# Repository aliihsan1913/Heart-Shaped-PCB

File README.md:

# Heart-Shaped LED PCB Design 

## Overview
This project features a custom heart-shaped PCB designed using **KiCad 9.0**. The goal was to combine electrical functionality with a unique form factor, suitable for decorative electronics or gift projects. 

## Visuals

*Figure 1: 3D Render of the heart-shaped board.*

*Figure 2: Complete circuit schematic.*

## Technical Details
* **CAD Tool:** KiCad 9.0
* **Shape:** Custom Heart Outline (Calculated using mathematical curves/coordinates).
* **Trace Design:** Curved traces to match the board's aesthetic.

## Components List
* **Light Emitting Diodes (LEDs):** 20x Red or Pink (SMD 0805 Package) arranged in a heart contour.
* **Power Source:** 3V CR2032 Coin Cell Battery (Düğme Pil).
* **Safety Feature:** Integrated PTC Fuse for overcurrent protection.
* **Control:** Mini Slide Switch (SPDT) for ON/OFF functionality.
* **Resistors:** 120Ω or 220Ω (SMD 0805) current-limiting resistors for LED longevity.
* **PCB:** Custom FR-4 substrate with a thickness of 1.6mm.

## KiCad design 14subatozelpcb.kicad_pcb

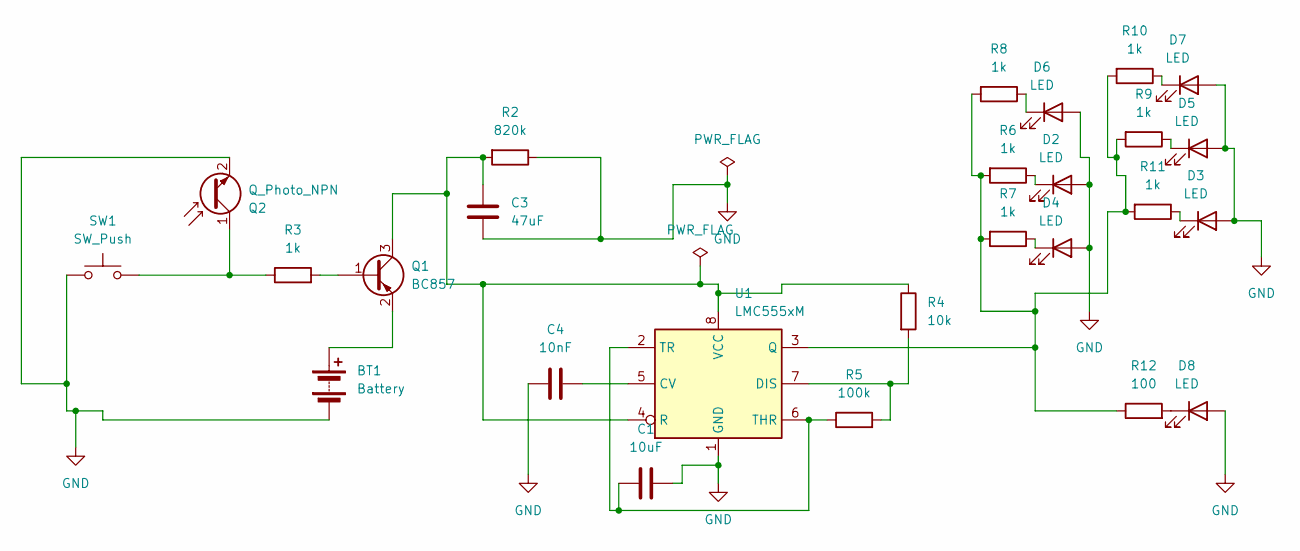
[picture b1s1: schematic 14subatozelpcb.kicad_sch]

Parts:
BT1: Battery; BatteryHolder_Keystone_3002_1x2032
C1: 10uF; R_0805_2012Metric
C3: 47uF; CP_EIA-3216-18_Kemet-A
C4: 10nF; R_0805_2012Metric
D2, D3, D4, D5, D6, D7, D8: LED; LED_0805_2012Metric
Q1: BC857; SOT-23
Q2: Q_Photo_NPN; SOT-23
R2: 820k; R_0805_2012Metric
R3, R6, R7, R8, R9, R10, R11: 1k; R_0805_2012Metric
R4: 10k; R_0805_2012Metric
R5: 100k; R_0805_2012Metric
R12: 100; R_0805_2012Metric
SW1: SW_Push; SW_SPST_TL3342
U1: LMC555xM; SOIC-8_3.9x4.9mm_P1.27mm

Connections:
GND: BT1.2 (-), C1.2, C3.2, C4.2, D2.2 (A), D3.2 (A), D4.2 (A), D5.2 (A), D6.2 (A), D7.2 (A), D8.2 (A), Q2.2 (E), R2.1, SW1.1, U1.1 (GND)
unnamed: BT1.1 (+), Q1.2 (E)
unnamed: D2.1 (K), R6.1
unnamed: D3.1 (K), R11.1
unnamed: D4.1 (K), R7.1
unnamed: D5.1 (K), R9.1
unnamed: D6.1 (K), R8.1
unnamed: D7.1 (K), R10.1
unnamed: D8.1 (K), R12.2
unnamed: Q1.1 (B), R3.2
unnamed: C3.1, Q1.3 (C), R2.2, R4.1, U1.4 (R), U1.8 (VCC)
unnamed: Q2.1 (C), R3.1, SW1.2
unnamed: C4.1, U1.5 (CV)
unnamed: R4.2, R5.2, U1.7 (DIS)
unnamed: R6.2, R7.2, R8.2, R9.2, R10.2, R11.2, R12.1, U1.3 (Q)
unnamed: C1.1, R5.1, U1.2 (TR), U1.6 (THR)

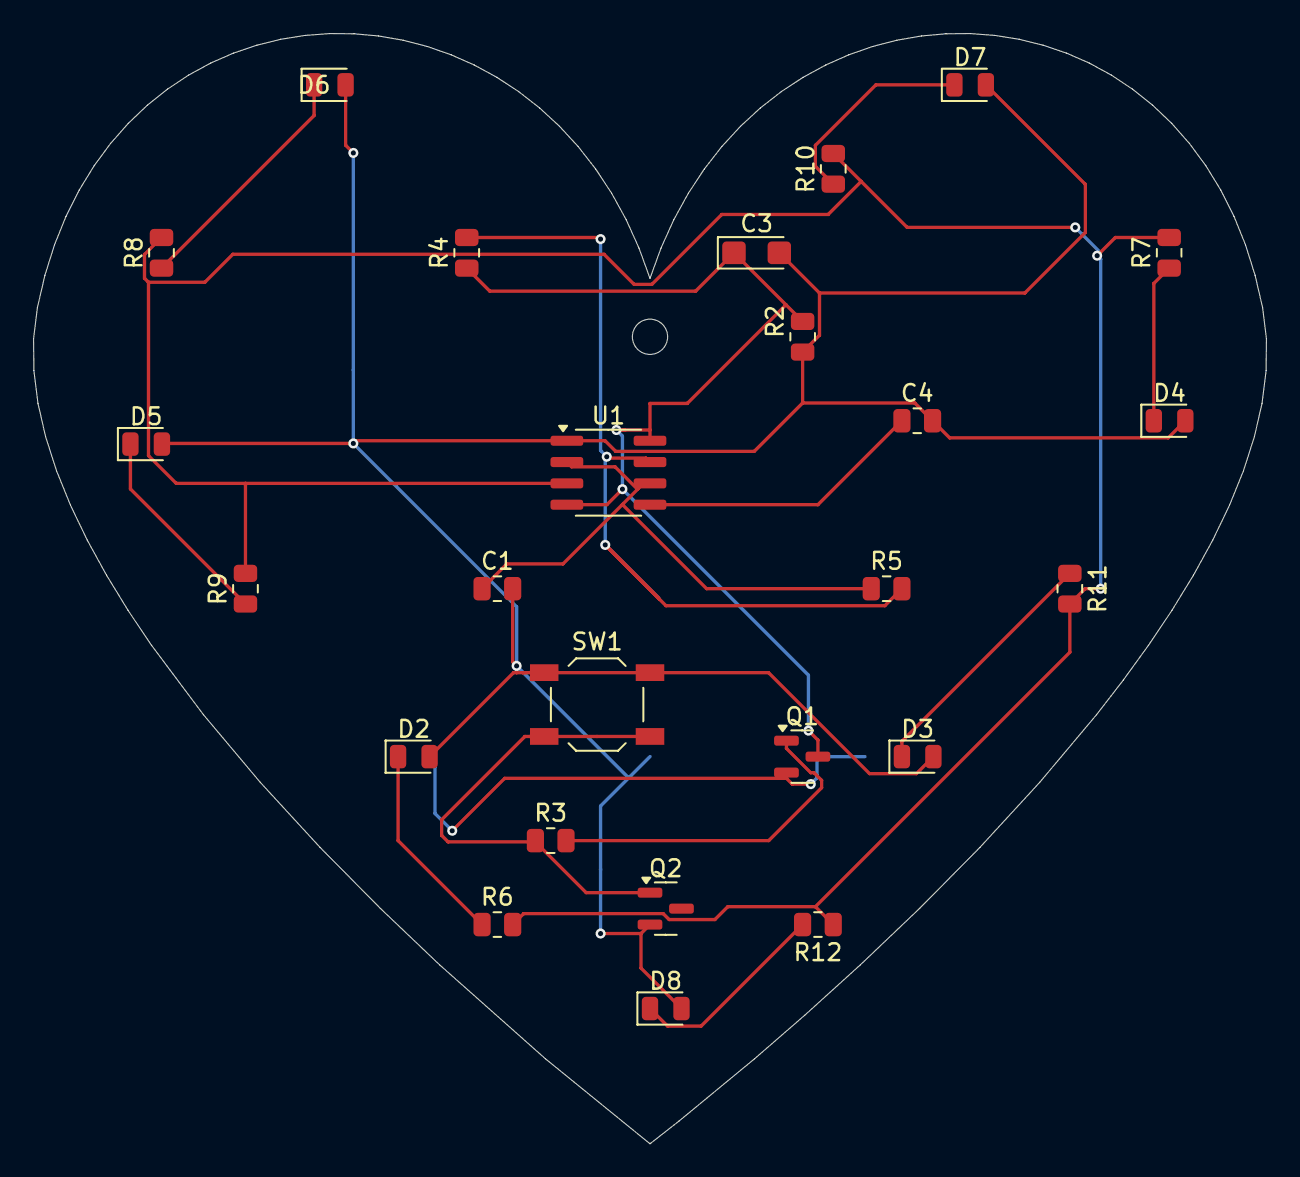
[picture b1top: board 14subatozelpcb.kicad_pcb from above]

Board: 2 copper layers, 73.4 x 66.1 mm, 26 parts (1 on the bottom side), 16 nets.

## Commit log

2026-02-05 Final hardware documentation with visuals and safety features
2026-02-05 Fixed README file extensions
2026-02-05 Fixed file extensions for README and images
